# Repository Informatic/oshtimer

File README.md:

OSHTimer
========
*the Open Source Hardware lap timer*

Introduction
------------
This project is targetted on developing open source and open hardware RC / FPV
racing lap timing system.

Technical description
---------------------
### Transponder
For initial proof-of-concept IR transponder with static Sony modulated code has
been chosen. Custom single-sided board based on AVR attiny*4 has been designed
and published in `transponder/` directory of this repository, however only
testing has been carried out on generic "Digispark"-like attiny84 board with IR
LED directly soldered to respective pins so far. Software is available in
`transponder-software/` directory of this repository. It uses
[Arduino-IRRemote library](https://github.com/z3t0/Arduino-IRremote), which has
to be installed beforehand. Migration to ino or platformio build system is
planned in near future.

### Receiver
Ground receiver consists of TSOP17**-like IR receiver connected to any
Arduino-compatible AVR board. Current testing has been carried out on custom
atmega32u4 board, however published code should work flawlessly on any atmega
microcontroller which would fit the sketch. Software for this part is available
in `receiver-software/` directory, and, same as transponder, uses
Arduino-IRRemote library.

License
-------
Software part of this project is published under **MIT license**, unless
otherwise specified.

Hardware part of this project is published under **CERN Open Hardware License**,
unless otherwise specified.

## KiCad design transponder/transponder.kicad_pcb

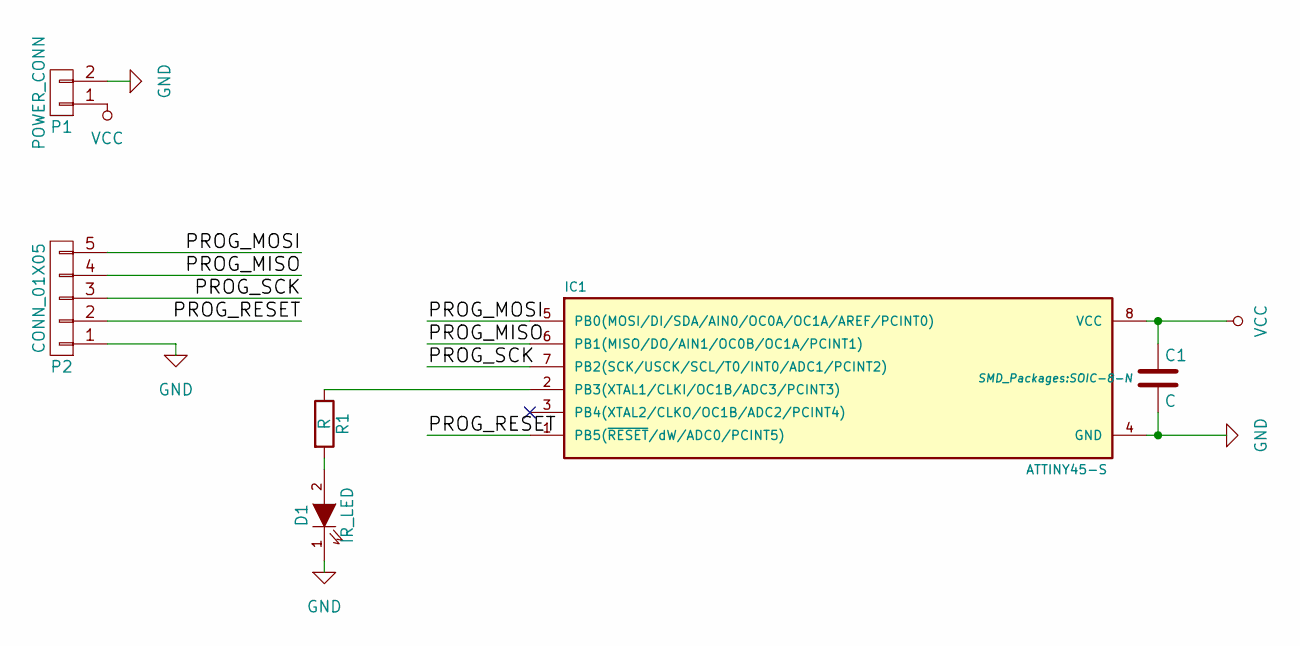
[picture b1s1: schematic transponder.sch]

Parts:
C1: C; C_0805_HandSoldering
D1: IR_LED; LED-5MM
IC1: ATTINY45-S; SOIC-8-N
P1: POWER_CONN; Pin_Header_Angled_1x02
P2: CONN_01X05; Pin_Header_Straight_1x05
R1: R; R_0805_HandSoldering

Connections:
/PROG_MISO: IC1.6 (PB1(MISO/DO/AIN1/OC0B/OC1A/PCINT1)), P2.4
/PROG_MOSI: IC1.5 (PB0(MOSI/DI/SDA/AIN0/OC0A/OC1A/AREF/PCI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), P2.5
/PROG_RESET: IC1.1 (PB5(~RESET~/dW/ADC0/PCINT5)), P2.2
/PROG_SCK: IC1.7 (PB2(SCK/USCK/SCL/T0/INT0/ADC1/PCINT2)), P2.3
GND: C1.2, D1.1 (K), IC1.4 (GND), P1.2, P2.1
unnamed: D1.2 (A), R1.2
unnamed: IC1.2 (PB3(XTAL1/CLKI/OC1B/ADC3/PCINT3)), R1.1
VCC: C1.1, IC1.8 (VCC), P1.1

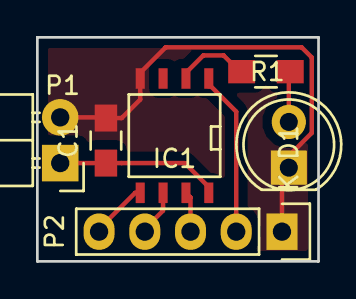
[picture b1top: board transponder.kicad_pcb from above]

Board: 2 copper layers, 15.6 x 12.4 mm, 6 parts (0 on the bottom side), 8 nets.

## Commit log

2015-10-06 First transponder schematic and PCB
2015-11-14 transponder: Rewire LED
2015-11-14 software: Initial PoC
2015-11-18 Add README
